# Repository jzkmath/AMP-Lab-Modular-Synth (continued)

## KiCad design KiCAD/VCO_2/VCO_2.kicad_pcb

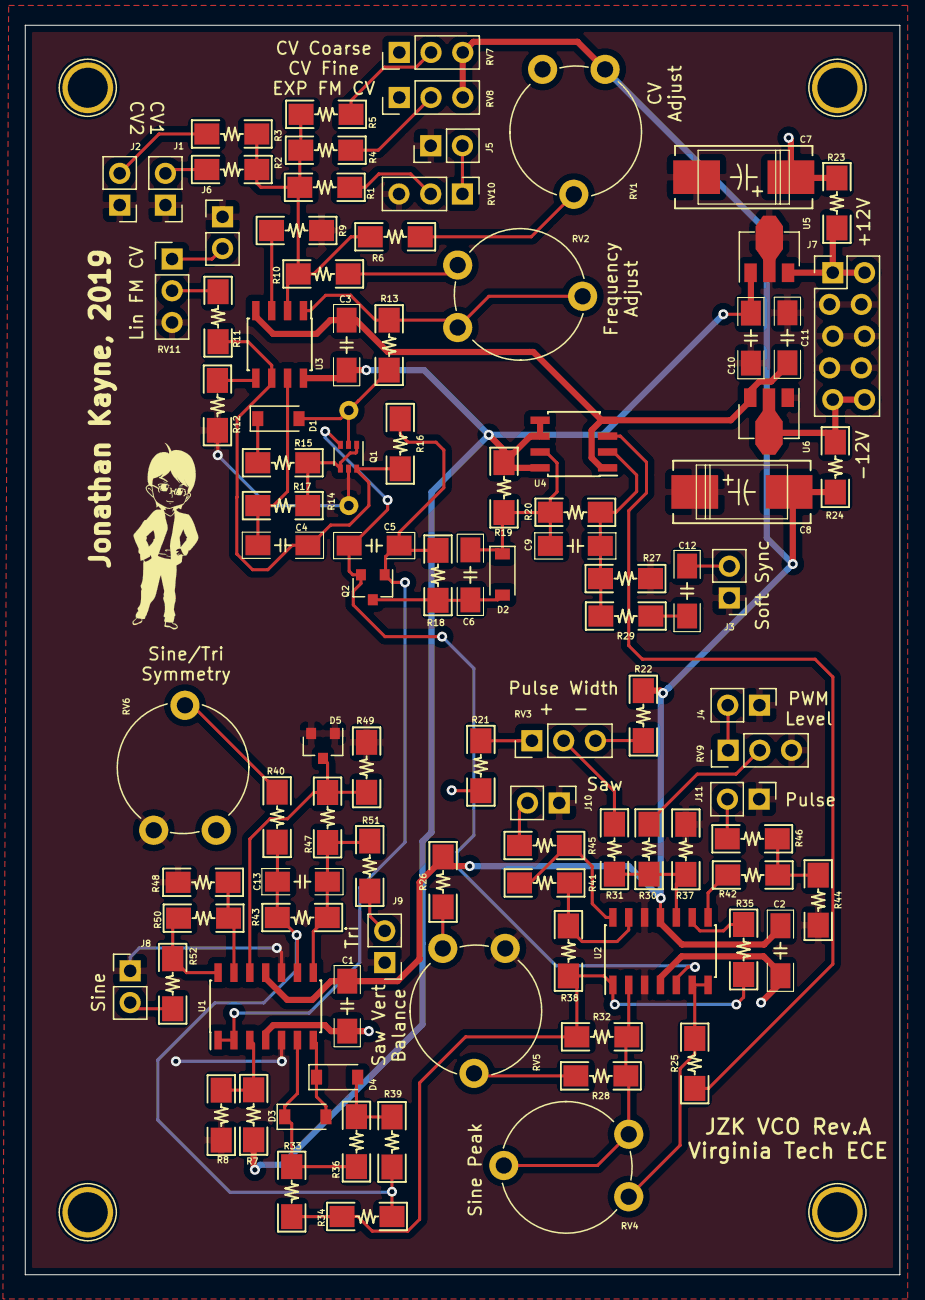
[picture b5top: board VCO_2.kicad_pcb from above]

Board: 2 copper layers, 70.0 x 100.0 mm, 100 parts (0 on the bottom side), 64 nets.

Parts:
C1, C2, C3, C10, C11: 100nF; C_1206
C4: 100pF; C_1206
C5: 220pF; C_1206
C6, C12, C13: 47pF; C_1206
C7, C8: 22uF; CP_Tantalum_7343
C9: 10pF; C_1206
D1, D2, D3, D4: 1N4148W; D_SOD-123
D5: BAV99; SOT-23
J1, J2, J3, J4, J5, J6, J8, J9, J10, J11: MJ-3502; PinHeader_1x02_P2.54mm_Vertical
J7: Power; PinHeader_2x05_P2.54mm_Vertical_Zigzag
Q1: BC857BS; SOT-363_SC-70-6
Q2: MMBFJ112; SOT-23
R1, R2, R3, R11, R12, R18, R28, R31, R33, R34, R36, R38, R41: 100k; R_1206
R4: 3.3M; R_1206
R5, R32: 220k; R_1206
R6, R37: 470k; R_1206
R7: 68k; R_1206
R8, R39: 50k; R_1206
R9: 47k; R_1206
R10, R19: 33k; R_1206
R13, R49: 22k; R_1206
R14: 1k Tempco; Tempco_Resistor_SOT363
R15, R16, R20: 1M; R_1206
R17, R25, R27, R29, R35, R42: 10k; R_1206
R21, R22: 7.5k; R_1206
R23, R24: 10; R_1206
R26: 5.6k; R_1206
R30: 180k; R_1206
R40, R47: 150k; R_1206
R43: 200k; R_1206
R44: 4.7k; R_1206
R45, R46, R51, R52: 1k; R_1206
R48: 1.5k; R_1206
R50: 15k; R_1206
RV1: 220k; Potentiometer_Piher_PT-10-V10_Vertical
RV2: 25k; Potentiometer_Piher_PT-10-V10_Vertical
RV3, RV7, RV8, RV9, RV10, RV11: 25k; PinHeader_1x03_P2.54mm_Vertical
RV4: 100k; Potentiometer_Piher_PT-10-V10_Vertical
RV5: 10k; Potentiometer_Piher_PT-10-V10_Vertical
RV6: 47k; Potentiometer_Piher_PT-10-V10_Vertical
U1, U2: TL074; SOIC-14_3.9x8.7mm_P1.27mm
U3: OPA2137; SOIC-8_3.9x4.9mm_P1.27mm
U4: LM311; SOIC-8_3.9x4.9mm_P1.27mm
U5: L78L12_SOT89; SOT-89-3
U6: L79L12_SOT89; SOT-89-3

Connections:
+12V: C1.1, C2.1, C7.1, R21.1, R23.2, RV1.1, RV6.1, RV7.1, RV8.1, U1.4, U2.4
+12VA: C3.1, C10.1, R7.1, R19.1, U3.8, U4.5, U4.6, U4.8, U5.1
+12V_IN: J7.1, J7.2, R23.1, U5.3
-12V: C1.2, C2.2, C8.2, R22.2, R24.2, R26.2, RV1.3, RV7.3, RV8.3, U1.11, U2.11
-12VA: C3.2, C11.2, U3.4, U4.1, U4.4, U6.3
-12V_IN: J7.9, J7.10, R24.1, U6.2
CV_Coarse: R5.2, RV7.2
CV_Fine: R4.2, RV8.2
EXP_CV1: J1.2, R2.2
EXP_CV2: J2.2, R3.2
EXP_FM_CV: R1.2, RV10.2
GND: C7.2, C8.1, C10.2, C11.1, D5.1, D5.2, J1.1, J2.1, J3.1, J4.1, J5.1, J6.1, J7.3, J7.4, J7.5, J7.6, J7.7, J7.8, J8.1, J9.1, J10.1, J11.1, Q1.5, R8.2, R9.2, R12.2, R14.2, R27.2, R37.2, R44.2, R48.2, R49.2, RV5.3, RV6.3, RV9.3, RV10.3, RV11.3, U1.5, U1.10, U2.3, U2.12, U5.2, U6.1
Hard_SYNC: C12.2, R29.1
LIN_FM_CV: R11.2, RV11.2
unnamed: C4.1, R17.2, U3.7
unnamed: C4.2, Q1.6, R11.1, R16.2, U3.6
unnamed: C5.1, Q2.1, R16.1, R18.2, U1.1, U1.2
unnamed: C5.2, Q1.3, Q2.2, U2.5
unnamed: C6.1, C9.2, D2.1, R19.2, R20.2, U4.7
unnamed: C6.2, D2.2, Q2.3, R18.1
unnamed: C9.1, R20.1, R27.1, R29.2, U4.2
unnamed: C13.1, R43.1, R47.2, R51.2, U1.8
unnamed: C13.2, R34.1, R39.2, R40.2, R43.2, U1.9
unnamed: D1.1, R15.2
unnamed: D1.2, Q1.2, R13.2, R14.1
unnamed: D3.1, R33.1, R36.2, U1.6
unnamed: D3.2, D4.1, U1.7
unnamed: D4.2, R36.1, R39.1
unnamed: D5.3, R47.1, R49.1, U1.12
unnamed: J4.2, RV9.1
unnamed: J5.2, RV10.1
unnamed: J6.2, RV11.1
unnamed: Q1.1, Q1.4, R15.1, R17.1
unnamed: R1.1, R2.1, R3.1, R4.1, R5.1, R6.1, R10.2, U3.2
unnamed: R6.2, RV1.2
unnamed: R7.2, R8.1, U1.3
unnamed: R9.1, U3.3
unnamed: R10.1, RV2.3
unnamed: R12.1, U3.5
unnamed: R13.1, RV2.1, RV2.2, U3.1
unnamed: R21.2, RV3.1
unnamed: R22.1, RV3.3
unnamed: R25.1, U4.3
unnamed: R25.2, RV4.3, U2.6, U2.7
unnamed: R26.1, RV5.1
unnamed: R28.1, R32.2, RV4.1, RV4.2, U2.2
unnamed: R28.2, RV5.2
unnamed: R30.1, R31.1, R37.1, U2.10
unnamed: R31.2, RV3.2
unnamed: R32.1, R33.2, R34.2, R35.2, R38.2, U2.1
unnamed: R35.1, U2.9
unnamed: R38.1, R41.2, U2.13
unnamed: R40.1, RV6.2
unnamed: R41.1, R45.2, U2.14
unnamed: R42.1, R44.1, R46.2
unnamed: R42.2, U2.8
unnamed: R48.1, R50.2, U1.13
unnamed: R50.1, R52.2, U1.14
PWM_CV: R30.2, RV9.2
Pulse: J11.2, R46.1
Sawtooth: J10.2, R45.1
Sine: J8.2, R52.1
Soft_SYNC: C12.1, J3.2
Triangle: J9.2, R51.1

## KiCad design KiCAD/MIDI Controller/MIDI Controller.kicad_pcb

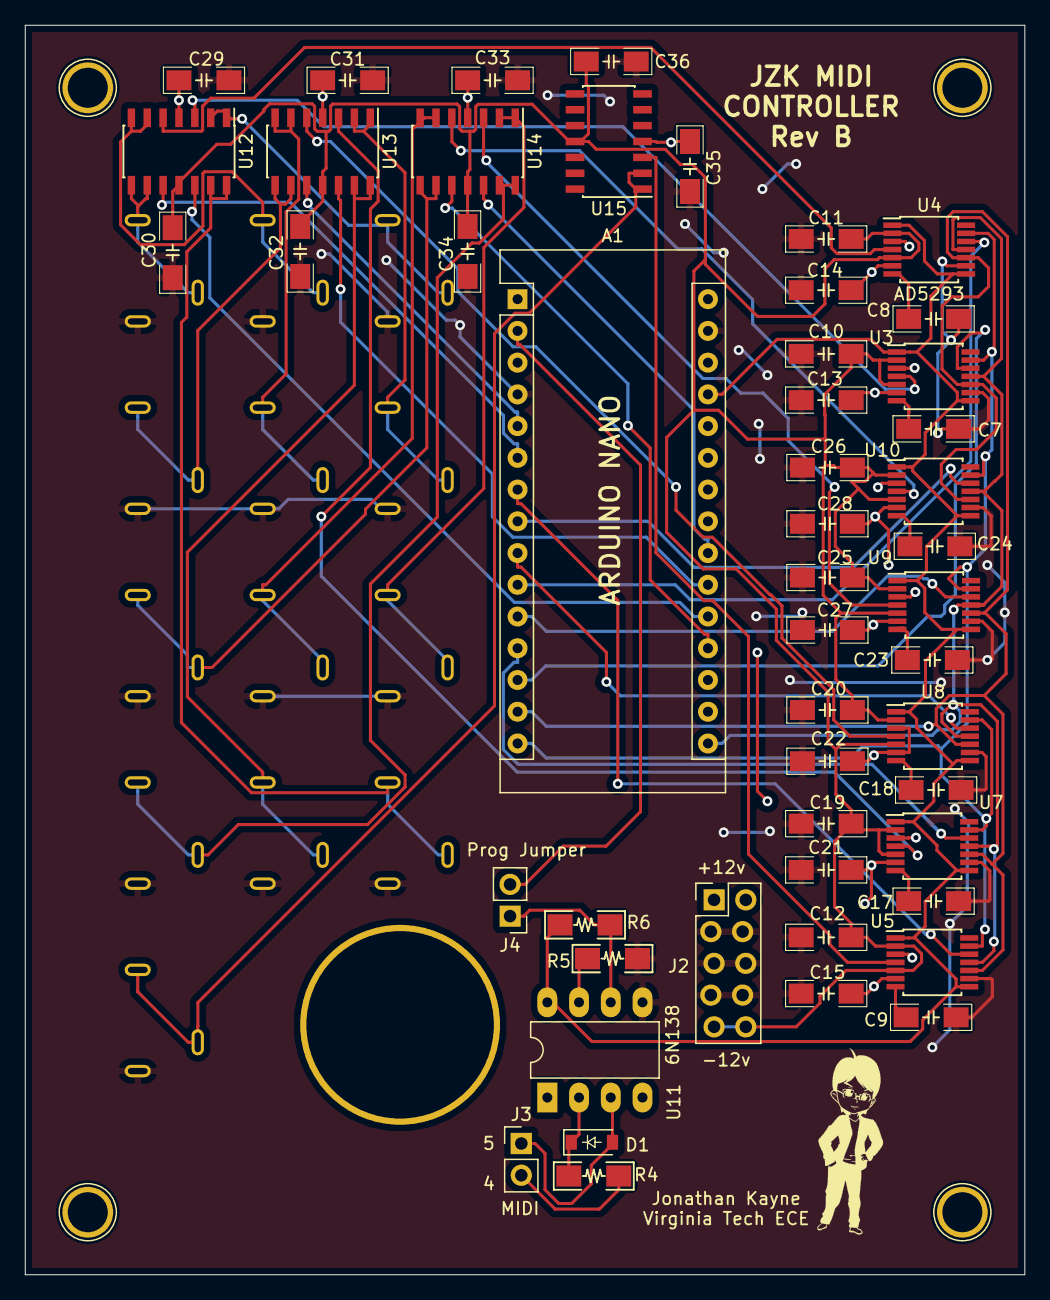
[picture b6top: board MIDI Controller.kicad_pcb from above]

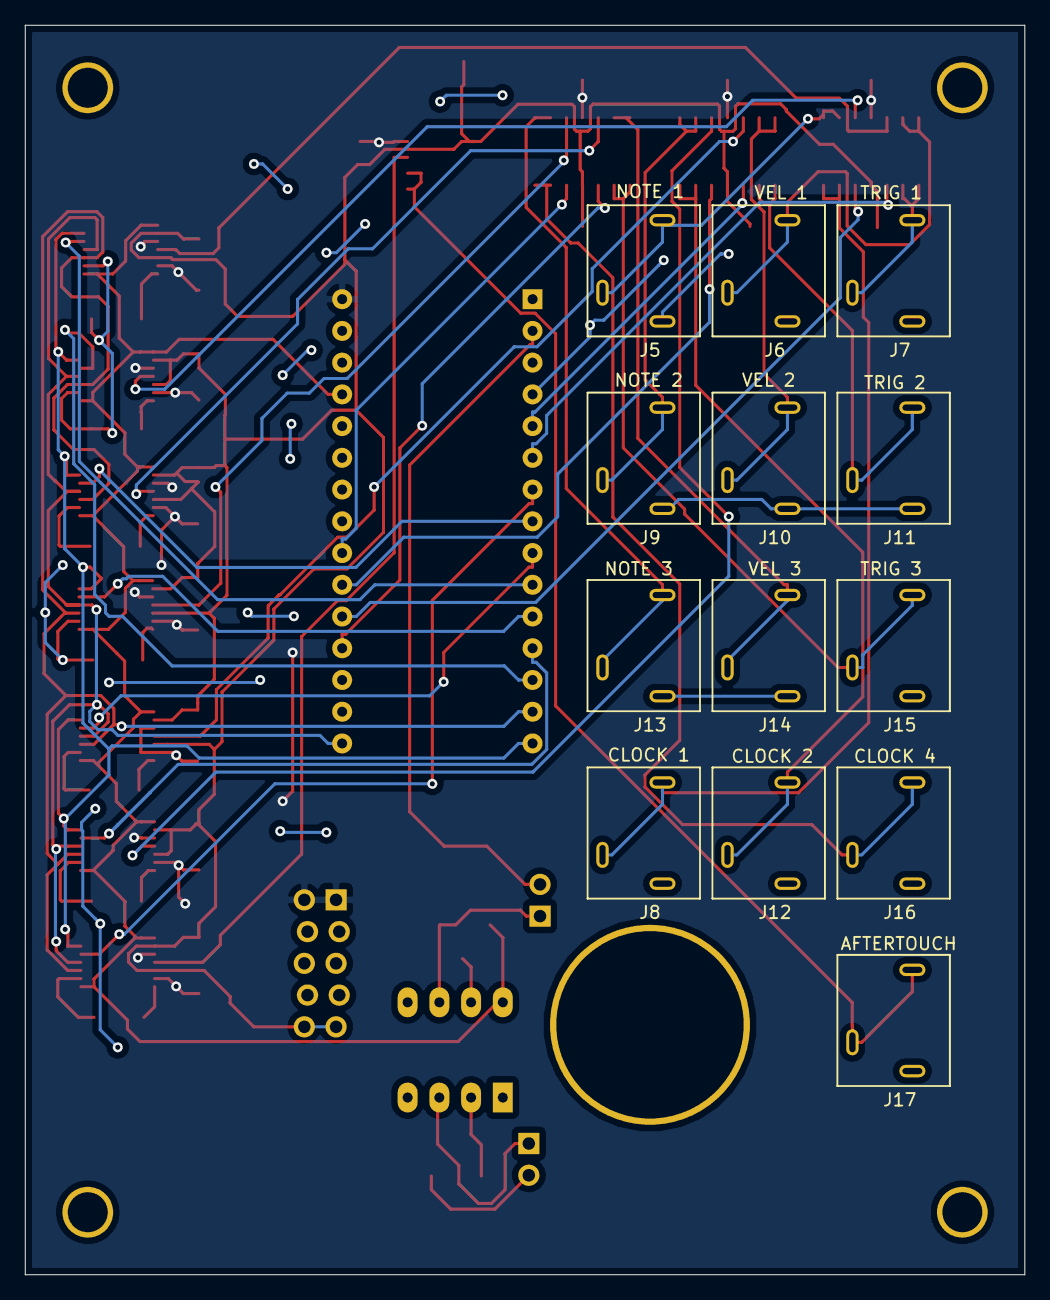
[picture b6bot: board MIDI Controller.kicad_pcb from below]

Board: 2 copper layers, 80.0 x 100.0 mm, 66 parts (13 on the bottom side), 53 nets.

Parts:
A1: Arduino_Nano_v3.x; Arduino_Nano
C7, C8, C9, C17, C18, C23, C24: 1uF; C_1206
C10, C11, C12, C13, C14, C15, C19, C20, C21, C22, C25, C26, C27, C28, C29, C30, C31, C32, C33, C34, C35, C36: 0.1uF; C_1206
D1: 1N4148W; D_SOD-123
J2: Power; PinHeader_2x05_P2.54mm_Vertical_Zigzag
J3: MIDI; PinHeader_1x02_P2.54mm_Vertical
J4: Prog Jumper; PinHeader_1x02_P2.54mm_Vertical
J5, J6, J7, J8, J9, J10, J11, J12, J13, J14, J15, J16, J17: 4832; Schurter_4832_Jack
R4, R6: 220; R_1206
R5: 4.7k; R_1206
SC1, SC2, SC3, SC4: M3_Screw_Hole
U3, U4, U5, U7, U8, U9, U10: AD5293; TSSOP-14_4.4x5mm_P0.65mm
U11: 6N138; DIP-8_W7.62mm_LongPads
U12, U13, U14, U15: TL074; SOIC-14_3.9x8.7mm_P1.27mm

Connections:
+5V: A1.27, R6.1, U3.1, U3.8, U4.1, U4.8, U5.1, U5.8, U7.1, U7.8, U8.1, U8.8, U9.1, U9.8, U10.1, U10.8, U11.8
+12V: A1.30, C13.2, C14.2, C15.2, C21.2, C22.2, C27.2, C28.2, C29.1, C31.1, C33.1, C35.1, J2.1, J2.2, U3.3, U3.6, U4.3, U4.6, U5.3, U5.6, U7.3, U7.6, U8.3, U8.6, U9.3, U9.6, U10.3, U10.6, U12.4, U13.4, U14.4, U15.4
-12V: C10.2, C11.2, C12.2, C19.2, C20.2, C25.2, C26.2, C30.2, C32.2, C34.2, C36.2, J2.9, J2.10, U3.2, U3.5, U4.2, U4.5, U5.2, U5.5, U7.2, U7.5, U8.2, U8.5, U9.2, U9.5, U10.2, U10.5, U12.11, U13.11, U14.11, U15.11
/External Pins/Aftertouch: J17.2, J17.3, U15.1, U15.2
/External Pins/Clock1: J8.2, J8.3, U12.13, U12.14
/External Pins/Clock2: J12.2, J12.3, U13.13, U13.14
/External Pins/Clock4: J16.2, J16.3, U14.13, U14.14
/External Pins/Note1: J5.2, J5.3, U12.1, U12.2
/External Pins/Note2: J9.2, J9.3, U13.1, U13.2
/External Pins/Note3: J13.2, J13.3, U14.1, U14.2
/External Pins/Trig1: J7.2, J7.3, U12.8, U12.9
/External Pins/Trig2: J11.2, J11.3, U13.8, U13.9
/External Pins/Trig3: J15.2, J15.3, U14.8, U14.9
/External Pins/Velocity1: J6.2, J6.3, U12.6, U12.7
/External Pins/Velocity2: J10.2, J10.3, U13.6, U13.7
/External Pins/Velocity3: J14.2, J14.3, U14.6, U14.7
CS1: A1.13, U3.12
CS2: A1.12, U7.12
CS3: A1.11, U9.12
CS4: A1.10, U4.12
CS5: A1.9, U8.12
CS6: A1.8, U10.12
CS7: A1.7, U5.12
CV1: U3.4, U12.3
CV2: U7.4, U13.3
CV3: U9.4, U14.3
CV4: U4.4, U12.5
CV5: U8.4, U13.5
CV6: U10.4, U14.5
CV7: U5.4, U15.3
GND: A1.4, A1.29, C7.2, C8.2, C9.2, C10.1, C11.1, C12.1, C13.1, C14.1, C15.1, C17.2, C18.2, C19.1, C20.1, C21.1, C22.1, C23.2, C24.2, C25.1, C26.1, C27.1, C28.1, C29.2, C30.1, C31.2, C32.1, C33.2, C34.1, C35.2, C36.1, J2.3, J2.4, J2.5, J2.6, J2.7, J2.8, J5.1, J6.1, J7.1, J8.1, J9.1, J10.1, J11.1, J12.1, J13.1, J14.1, J15.1, J16.1, J17.1, R5.2, U3.9, U4.9, U5.9, U7.9, U8.9, U9.9, U10.9, U11.5
MCU_Clock_1: A1.20, U12.12
MCU_Clock_2: A1.21, U13.12
MCU_Clock_4: A1.22, U14.12
MCU_Trig1: A1.6, U12.10
MCU_Trig2: A1.5, U13.10
MCU_Trig3: A1.19, U14.10
MIDI_Rx: J4.1, R6.2, U11.6
MISO: A1.15, U3.13, U4.13, U5.13, U7.13, U8.13, U9.13, U10.13
MOSI: A1.14, U3.10, U4.10, U5.10, U7.10, U8.10, U9.10, U10.10
unnamed: A1.2, J4.2
unnamed: C7.1, U3.7
unnamed: C8.1, U4.7
unnamed: C9.1, U5.7
unnamed: C17.1, U7.7
unnamed: C18.1, U8.7
unnamed: C23.1, U9.7
unnamed: C24.1, U10.7
unnamed: D1.1, R4.1, U11.2
unnamed: D1.2, J3.5, U11.3
unnamed: J3.4, R4.2
unnamed: R5.1, U11.7
SCK: A1.16, U3.11, U4.11, U5.11, U7.11, U8.11, U9.11, U10.11

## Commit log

2019-05-06 Added VCO
2019-05-07 updated VCO2
2019-05-07 Update render
2019-05-11 added VCF
2019-05-12 added voltage regulator to VCF
2019-05-17 update EG
2019-05-18 added MIDI Controller
2019-05-27 Added RevB and VCA
2019-05-27 update pics
2019-05-29 Added MIDI controller and PSU
